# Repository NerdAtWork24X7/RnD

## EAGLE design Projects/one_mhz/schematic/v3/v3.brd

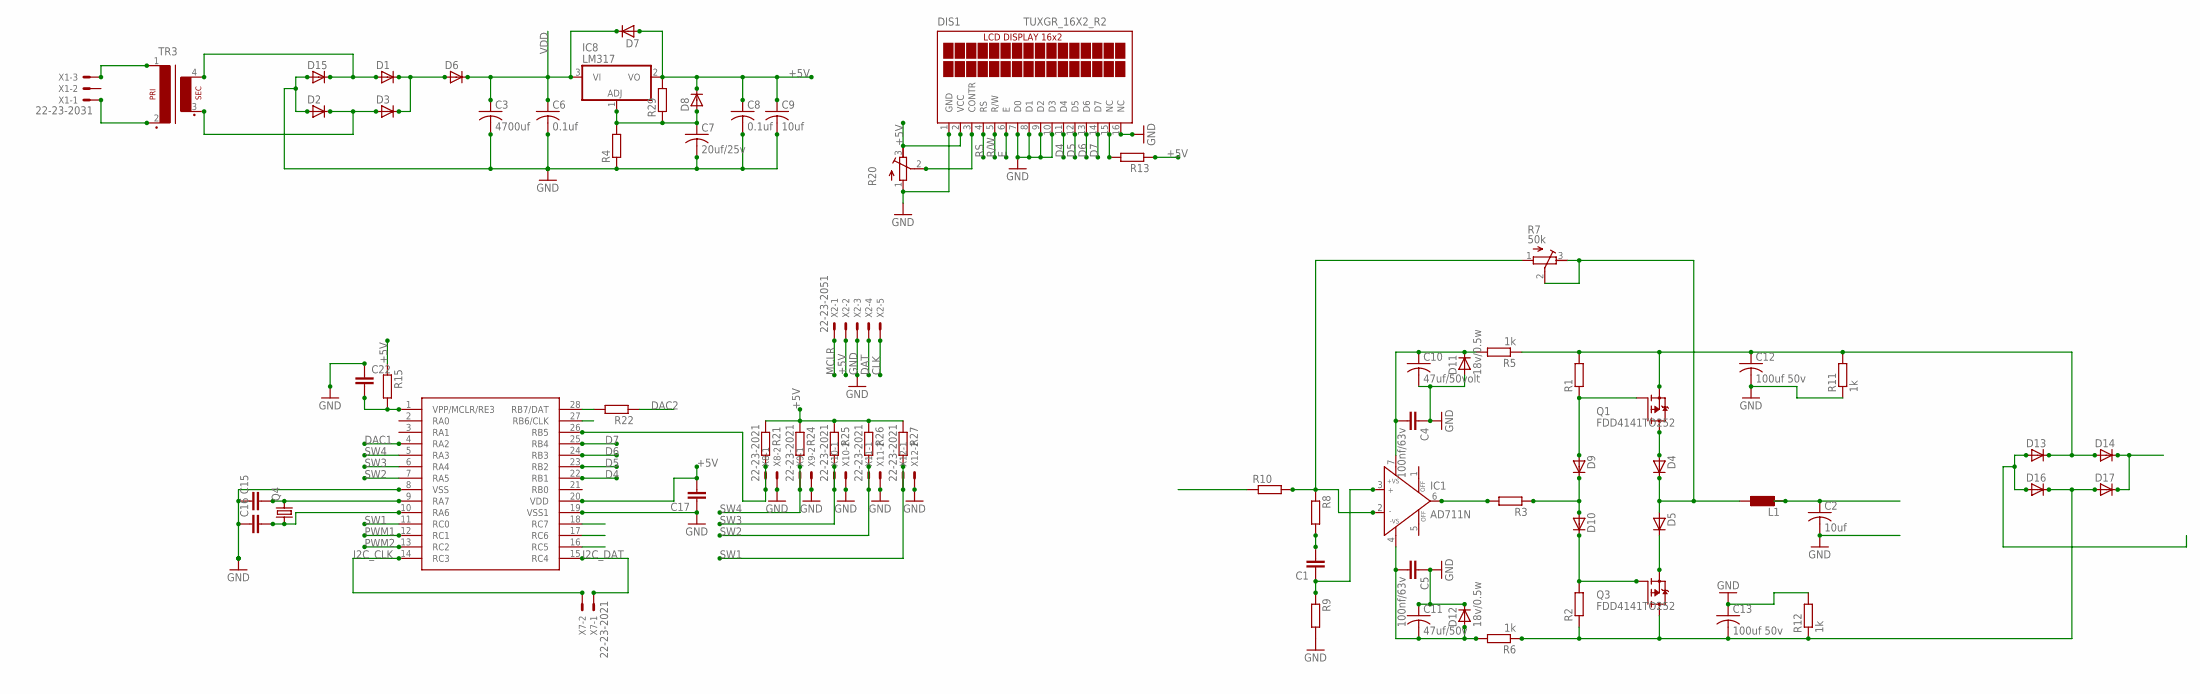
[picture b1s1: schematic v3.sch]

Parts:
C1, C15, C16, C17, C22: CC0603; C0603
C2, C9: 10uf; C025-025X050
C3: 4700uf; C025-025X050
C4, C5: 100nf/63v; C0603
C6, C8: 0.1uf; C025-025X050
C7: 20uf/25v; C025-025X050
C10: 47uf/50volt; C025-025X050
C11: 47uf/50v; C025-025X050
C12, C13: 100uf 50v; C025-025X050
D1, D2, D3, D4, D5, D6, D7, D8, D9, D10, D13, D14, D15, D16, D17: D-SOD-87; SOD87
D11, D12: 18v/0.5w; SOD87
DIS1: TUXGR_16X2_R2
IC1: AD711N; DIL08
IC8: LM317; TO92
L1: L0204/7; 0204/7
Q1, Q3: FDD4141TO252; TO252
Q4: CRYSTALHC49U-V; HC49U-V
R1, R2, R3, R4, R8, R9, R10, R13, R15, R21, R22, R24, R25, R26, R27, R29: R-EU_R0603; R0603
R5, R6, R11, R12: 1k; R0603
R7: 50k; RTRIM64X
R20: R-TRIMM64X; RTRIM64X
TR3: VR13-1
U$1: PIC16F15345; SO28W
X1: 22-23-2031
X2: 22-23-2051
X7, X8, X9, X10, X11, X12: 22-23-2021

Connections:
+5V: C8.1, C9.1, C17.2, D7.2 (A), D8.1 (C), DIS1.2 (VCC), IC8.2 (VO), R13.1, R15.1, R20.3 (E), R21.1, R24.1, R25.1, R26.1, R27.1, R29.2, U$1.20 (VDD), X2.2
CLK: U$1.27 (RB6/CLK), X2.5
D4: DIS1.11 (D4), U$1.22 (RB1)
D5: DIS1.12 (D5), U$1.23 (RB2)
D6: DIS1.13 (D6), U$1.24 (RB3)
D7: DIS1.14 (D7), U$1.25 (RB4)
DAC1: U$1.4 (RA2)
DAC2: R22.1
DAT: R22.2, U$1.28 (RB7/DAT), X2.4
E: DIS1.6 (E), U$1.18 (RC7)
GND: C2.2, C3.2, C4.1, C5.1, C6.2, C7.2, C8.2, C9.2, C10.2, C11.1, C12.2, C13.1, C15.1, C16.1, C17.1, C22.1, D2.2 (A), D11.2 (A), D12.1 (C), D15.2 (A), DIS1.1 (GND), DIS1.7 (D0), DIS1.8 (D1), DIS1.9 (D2), DIS1.10 (D3), DIS1.16 (NC), R4.1, R9.2, R11.1, R12.2, R20.1 (A), U$1.8 (VSS), U$1.19 (VSS1), X2.3, X8.2, X9.2, X10.2, X11.2, X12.2
GND1: D13.2 (A), D16.2 (A)
I2C_CLK: U$1.14 (RC3), X7.2
I2C_DAT: U$1.15 (RC4), X7.1
MCLR: C22.2, R15.2, U$1.1 (VPP/MCLR/RE3), X2.1
unnamed: D4.1 (C), D5.2 (A), L1.1, R7.2 (S), R7.3 (E)
unnamed: D4.2 (A), Q1.3 (D)
unnamed: D1.1 (C), D3.1 (C), D6.2 (A)
unnamed: D1.2 (A), D15.1 (C), TR3.4 (S4)
unnamed: D2.1 (C), D3.2 (A), TR3.3 (S3)
unnamed: D5.1 (C), Q3.2 (S)
unnamed: D9.1 (C), D10.2 (A), R3.1
unnamed: DIS1.15 (NC), R13.2
unnamed: D10.1 (C), Q3.1 (G), R2.2
unnamed: C7.1, D8.2 (A), IC8.1 (ADJ), R4.2, R29.1
unnamed: R21.2, U$1.26 (RB5), X8.1
unnamed: D9.2 (A), Q1.1 (G), R1.1
unnamed: IC1.6 (OUT), R3.2
unnamed: C5.2, C11.2, D12.2 (A), IC1.4 (-VS), R6.2
unnamed: C4.2, C10.1, D11.1 (C), IC1.7 (+VS), R5.2
unnamed: DIS1.3 (CONTR), R20.2 (S)
unnamed: C1.2, R8.2
unnamed: IC1.2 (IN-), R7.1 (A), R8.1, R10.2
unnamed: C1.1, IC1.3 (IN+), R9.1
unnamed: C2.1, L1.2
unnamed: D14.1 (C), D17.1 (C)
unnamed: C12.1, D13.1 (C), D14.2 (A), Q1.2 (S), R1.2, R5.1, R11.2
unnamed: TR3.1, X1.3
unnamed: TR3.2, X1.1
unnamed: C16.2, Q4.1, U$1.10 (RA6)
unnamed: C15.2, Q4.2, U$1.9 (RA7)
unnamed: C13.2, D16.1 (C), D17.2 (A), Q3.3 (D), R2.1, R6.1, R12.1
PWM1: U$1.12 (RC1)
PWM2: U$1.13 (RC2)
R/W: DIS1.5 (R/W), U$1.17 (RC6)
RS: DIS1.4 (RS), U$1.16 (RC5)
SW1: R27.2, U$1.11 (RC0), X12.1
SW2: R26.2, U$1.7 (RA5), X11.1
SW3: R25.2, U$1.6 (RA4), X10.1
SW4: R24.2, U$1.5 (RA3), X9.1
VDD: C3.1, C6.1, D6.1 (C), D7.1 (C), IC8.3 (VI)

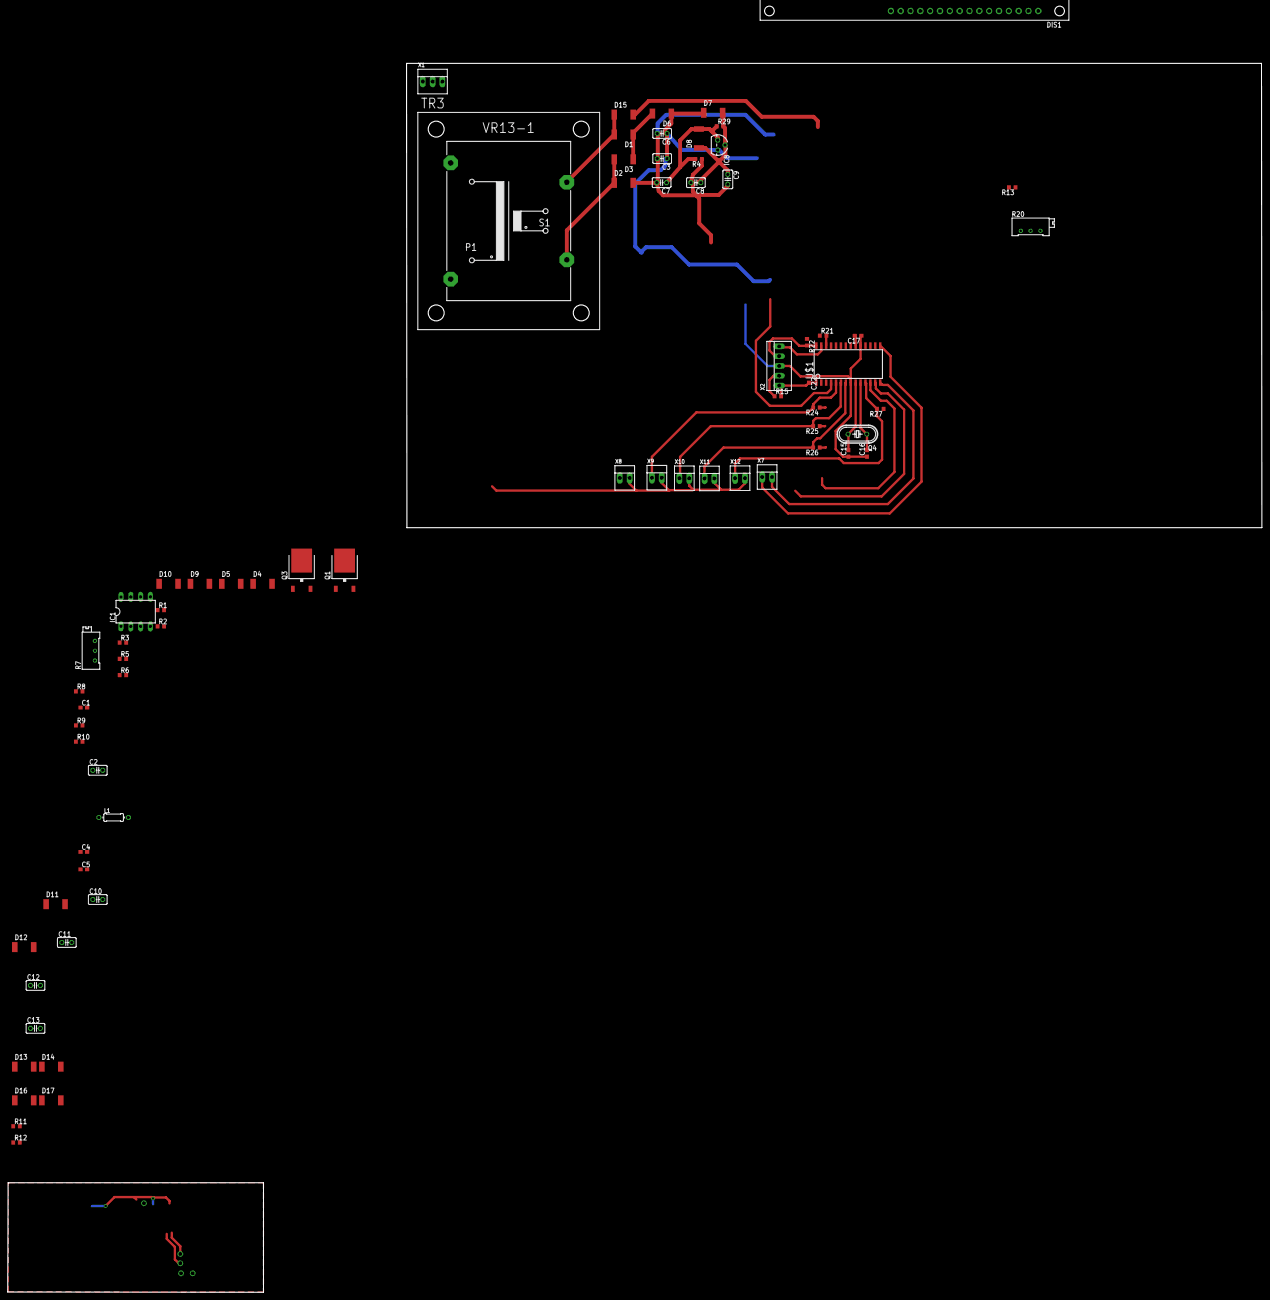
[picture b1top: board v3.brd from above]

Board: 2 copper layers, 324.1 x 317.6 mm, 73 parts (0 on the bottom side), 47 nets.

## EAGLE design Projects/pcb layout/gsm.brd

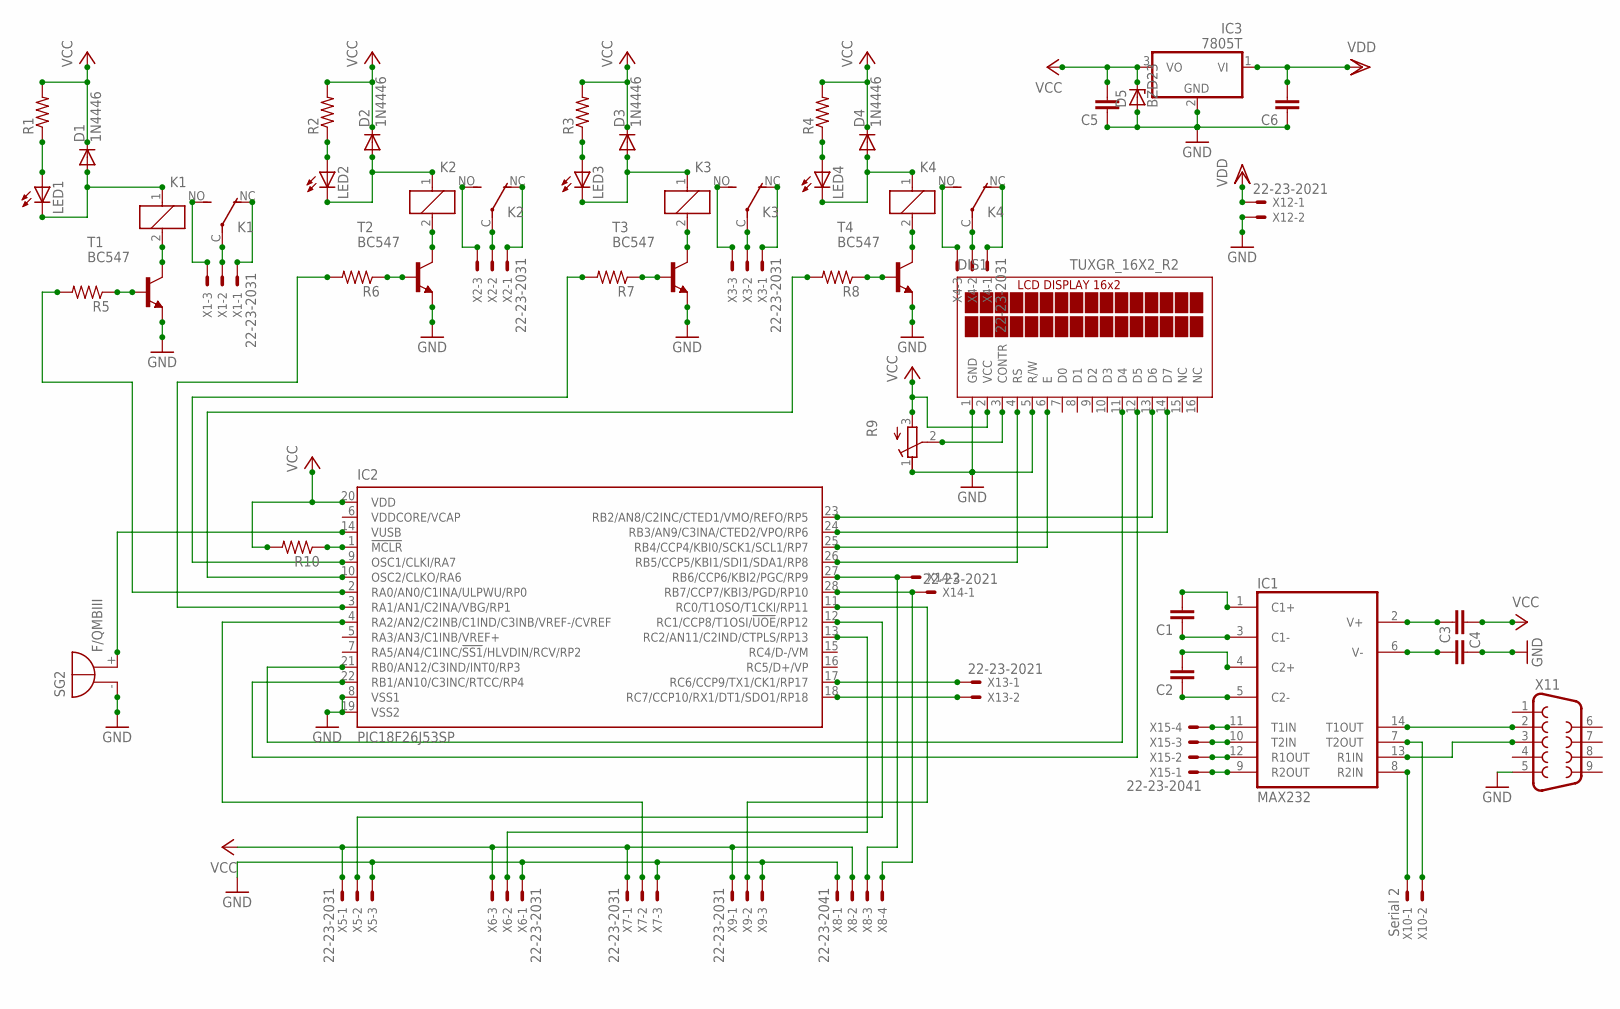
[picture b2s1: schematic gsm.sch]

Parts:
C1, C2, C3, C4, C5, C6: C2.5/2; C2.5-2
D1, D2, D3, D4: 1N4446; DO35-10
D5: BZD23; SOD81
DIS1: TUXGR_16X2_R2
IC1: MAX232; DIL16
IC2: PIC18F26J53SP; DIL28-3
IC3: 7805T; TO220H
K1, K2, K3, K4: JJM1-12V; JJM1C
LED1, LED2, LED3, LED4: LED3MM
R1, R2, R3, R4, R5, R6, R7, R8, R10: R-US_0207/10; 0207/10
R9: R-TRIMMT93YA; RTRIMT93YA
SG2: F/QMBIII
T1, T2, T3, T4: BC547; TO92
X1, X2, X3, X4, X5, X6, X7, X9: 22-23-2031
X8, X15: 22-23-2041
X10: Serial 2; 22-23-2021
X11: F09H
X12, X13, X14: 22-23-2021

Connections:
FIRERELAY: IC2.2 (RA0/AN0/C1INA/ULPWU/RP0), R5.2
GND: C3.2, C5.1, C6.1, D5.A, DIS1.1 (GND), DIS1.5 (R/W), IC1.15 (GND), IC2.8 (VSS1), IC2.19 (VSS2), IC3.2 (GND), R9.1 (E), SG2.- (+), T1.1 (E), T2.1 (E), T3.1 (E), T4.1 (E), X5.3, X6.1, X7.3, X8.1, X9.3, X11.5, X12.2
unnamed: K4.NC (O), X4.1
unnamed: LED1.A, R1.1
unnamed: D1.A, K1.1, LED1.K (C)
unnamed: K4.C, X4.2
unnamed: LED2.A, R2.1
unnamed: D2.A, K2.1, LED2.K (C)
unnamed: K4.NO (S), X4.3
unnamed: LED3.A, R3.1
unnamed: D3.A, K3.1, LED3.K (C)
unnamed: K3.NC (O), X3.1
unnamed: LED4.A, R4.1
unnamed: D4.A, K4.1, LED4.K (C)
unnamed: K1.2, T1.3 (C)
unnamed: K2.2, T2.3 (C)
unnamed: K3.2, T3.3 (C)
unnamed: K4.2, T4.3 (C)
unnamed: R5.1, T1.2 (B)
unnamed: R6.1, T2.2 (B)
unnamed: R7.1, T3.2 (B)
unnamed: R8.1, T4.2 (B)
unnamed: IC2.3 (RA1/AN1/C2INA/VBG/RP1), R6.2
unnamed: IC2.9 (OSC1/CLKI/RA7), R7.2
unnamed: IC2.10 (OSC2/CLKO/RA6), R8.2
unnamed: DIS1.14 (D7), IC2.24 (RB3/AN9/C3INA/CTED2/VPO/RP6)
unnamed: DIS1.13 (D6), IC2.23 (RB2/AN8/C2INC/CTED1/VMO/REFO/RP5)
unnamed: DIS1.12 (D5), IC2.22 (RB1/AN10/C3INC/RTCC/RP4)
unnamed: DIS1.11 (D4), IC2.21 (RB0/AN12/C3IND/INT0/RP3)
unnamed: DIS1.6 (E), IC2.25 (RB4/CCP4/KBI0/SCK1/SCL1/RP7)
unnamed: DIS1.4 (RS), IC2.26 (RB5/CCP5/KBI1/SDI1/SDA1/RP8)
unnamed: DIS1.3 (CONTR), R9.2 (S)
unnamed: K3.C, X3.2
unnamed: K3.NO (S), X3.3
unnamed: K2.C, X2.2
unnamed: K2.NC (O), X2.1
unnamed: K2.NO (S), X2.3
unnamed: K1.C, X1.2
unnamed: K1.NC (O), X1.1
unnamed: K1.NO (S), X1.3
unnamed: C1.2, IC1.1 (C1+)
unnamed: C1.1, IC1.3 (C1-)
unnamed: C2.2, IC1.4 (C2+)
unnamed: C2.1, IC1.5 (C2-)
unnamed: C4.2, IC1.2 (V+)
unnamed: C3.1, IC1.6 (V-)
unnamed: IC2.17 (RC6/CCP9/TX1/CK1/RP17), X13.1
unnamed: IC1.10 (T2IN), X15.3
unnamed: IC2.12 (RC1/CCP8/T1OSI/!UOE!/RP12), X5.2
unnamed: IC2.13 (RC2/AN11/C2IND/CTPLS/RP13), X6.2
unnamed: IC2.4 (RA2/AN2/C2INB/C1IND/C3INB/VREF-/CVREF), X7.2
unnamed: IC1.11 (T1IN), X15.4
unnamed: IC1.12 (R1OUT), X15.2
unnamed: IC2.27 (RB6/CCP6/KBI2/PGC/RP9), X8.3, X14.2
unnamed: IC2.1 (!MCLR), R10.1
unnamed: IC2.11 (RC0/T1OSO/T1CKI/RP11), X9.2
unnamed: IC2.14 (VUSB), SG2.+ (-)
unnamed: IC2.28 (RB7/CCP7/KBI3/PGD/RP10), X8.4, X14.1
unnamed: IC1.13 (R1IN), X11.3
unnamed: IC1.14 (T1OUT), X11.2
unnamed: IC1.7 (T2OUT), X10.2
unnamed: IC1.8 (R2IN), X10.1
unnamed: IC2.18 (RC7/CCP10/RX1/DT1/SDO1/RP18), X13.2
unnamed: IC1.9 (R2OUT), X15.1
VCC: C4.1, C5.2, D1.C, D2.C, D3.C, D4.C, D5.C, DIS1.2 (VCC), IC1.16 (VCC), IC2.20 (VDD), IC3.3 (VO), R1.2, R2.2, R3.2, R4.2, R9.3 (A), R10.2, X5.1, X6.3, X7.1, X8.2, X9.1
VDD: C6.2, IC3.1 (VI), X12.1

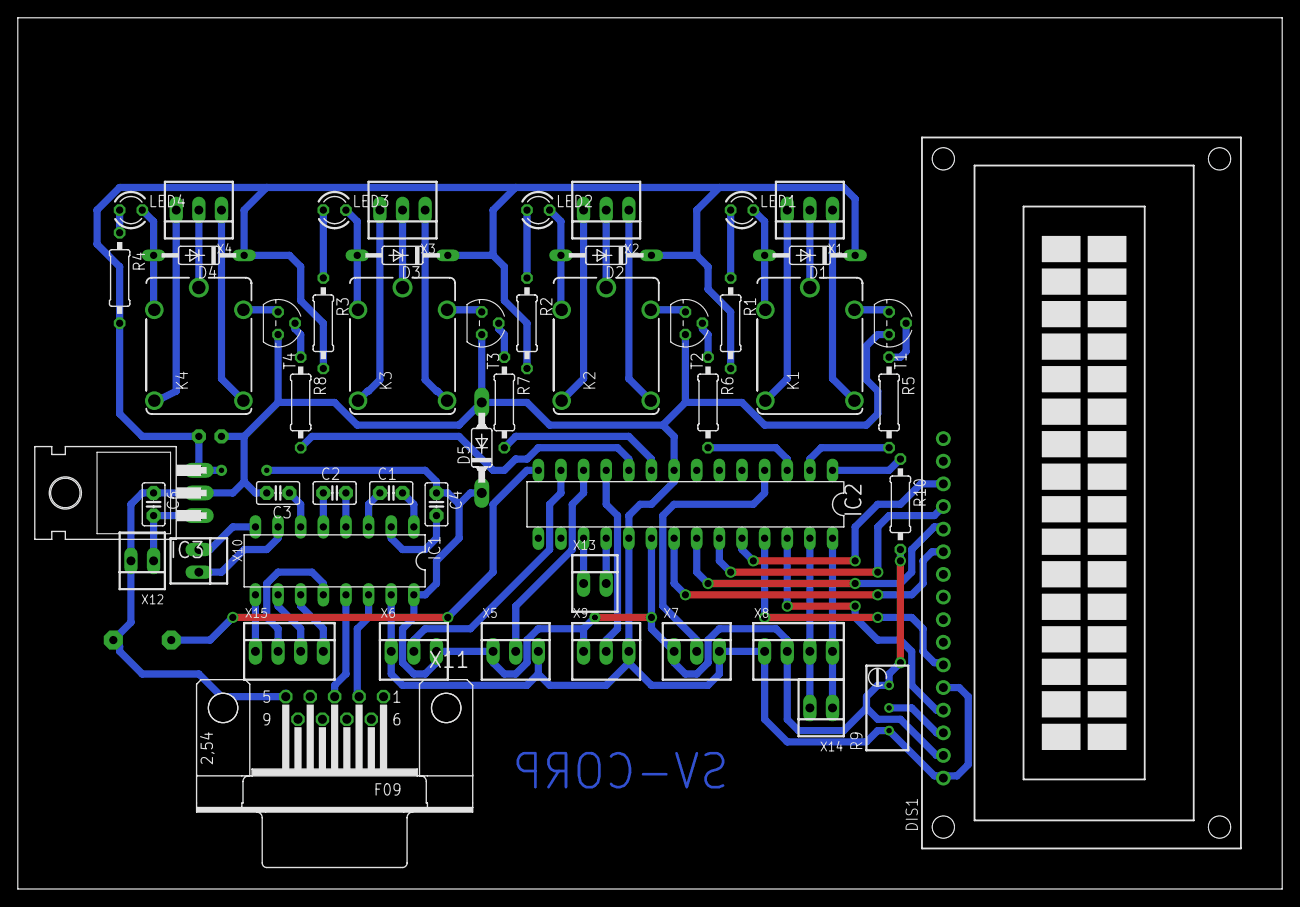
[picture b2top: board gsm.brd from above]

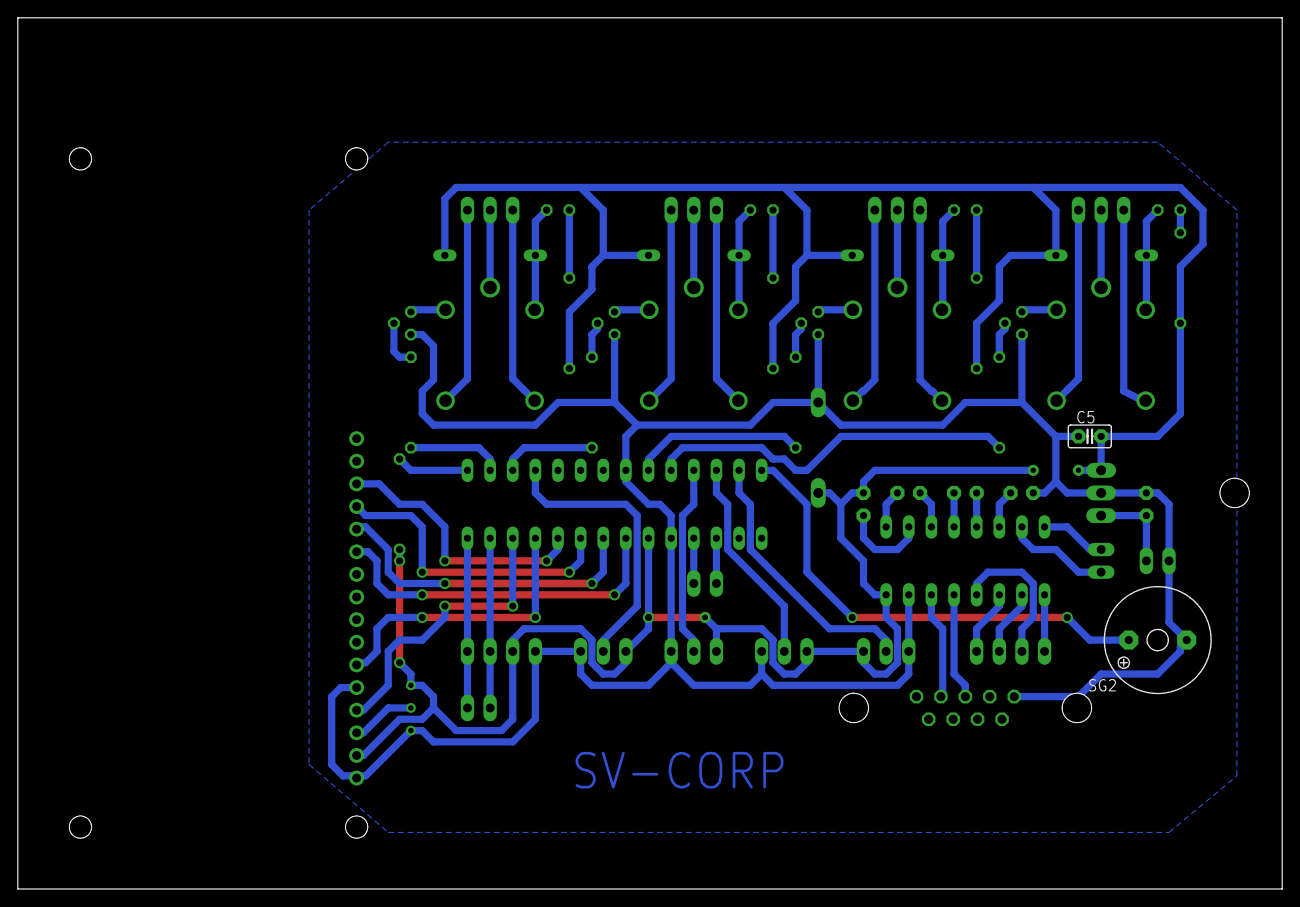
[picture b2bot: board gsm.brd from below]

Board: 2 copper layers, 141.9 x 97.8 mm, 53 parts (2 on the bottom side), 66 nets.

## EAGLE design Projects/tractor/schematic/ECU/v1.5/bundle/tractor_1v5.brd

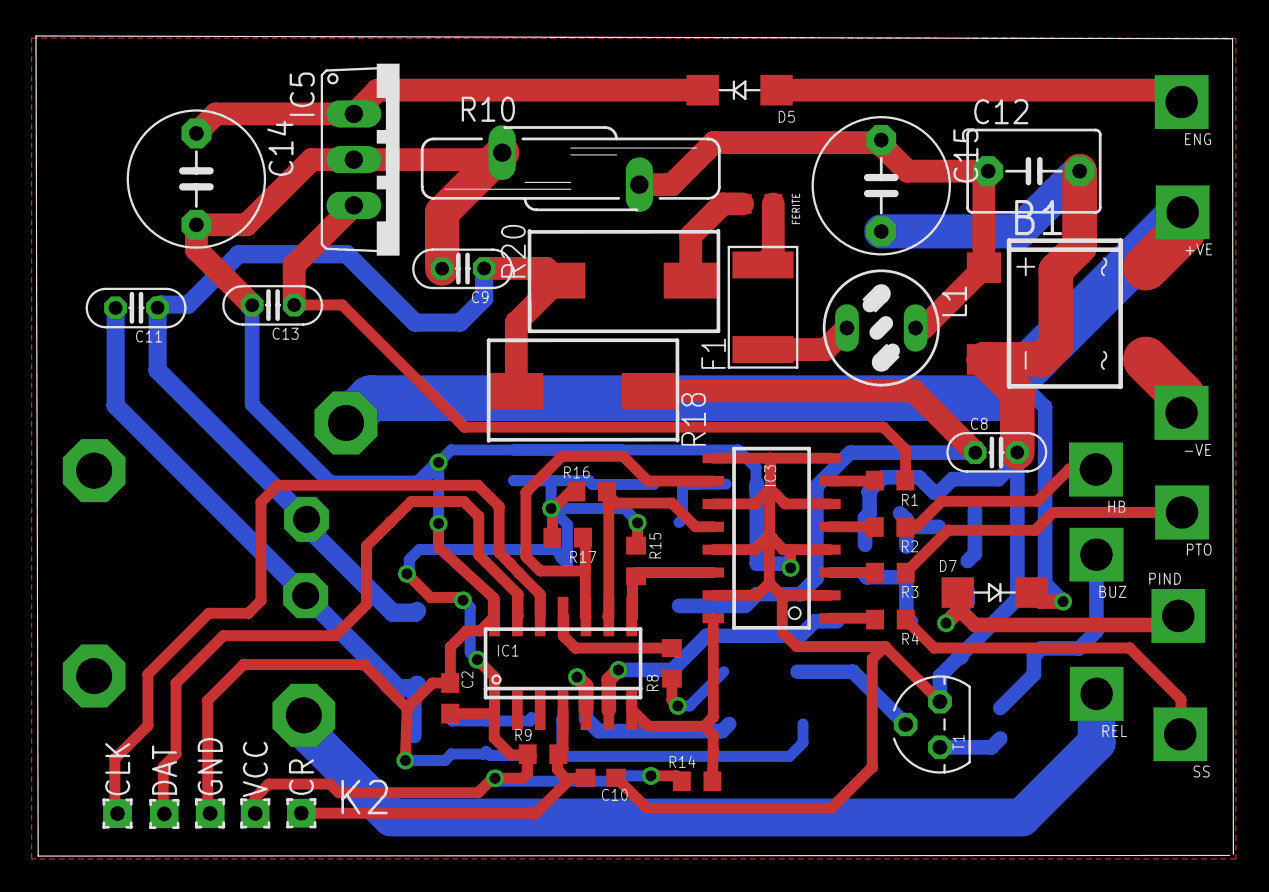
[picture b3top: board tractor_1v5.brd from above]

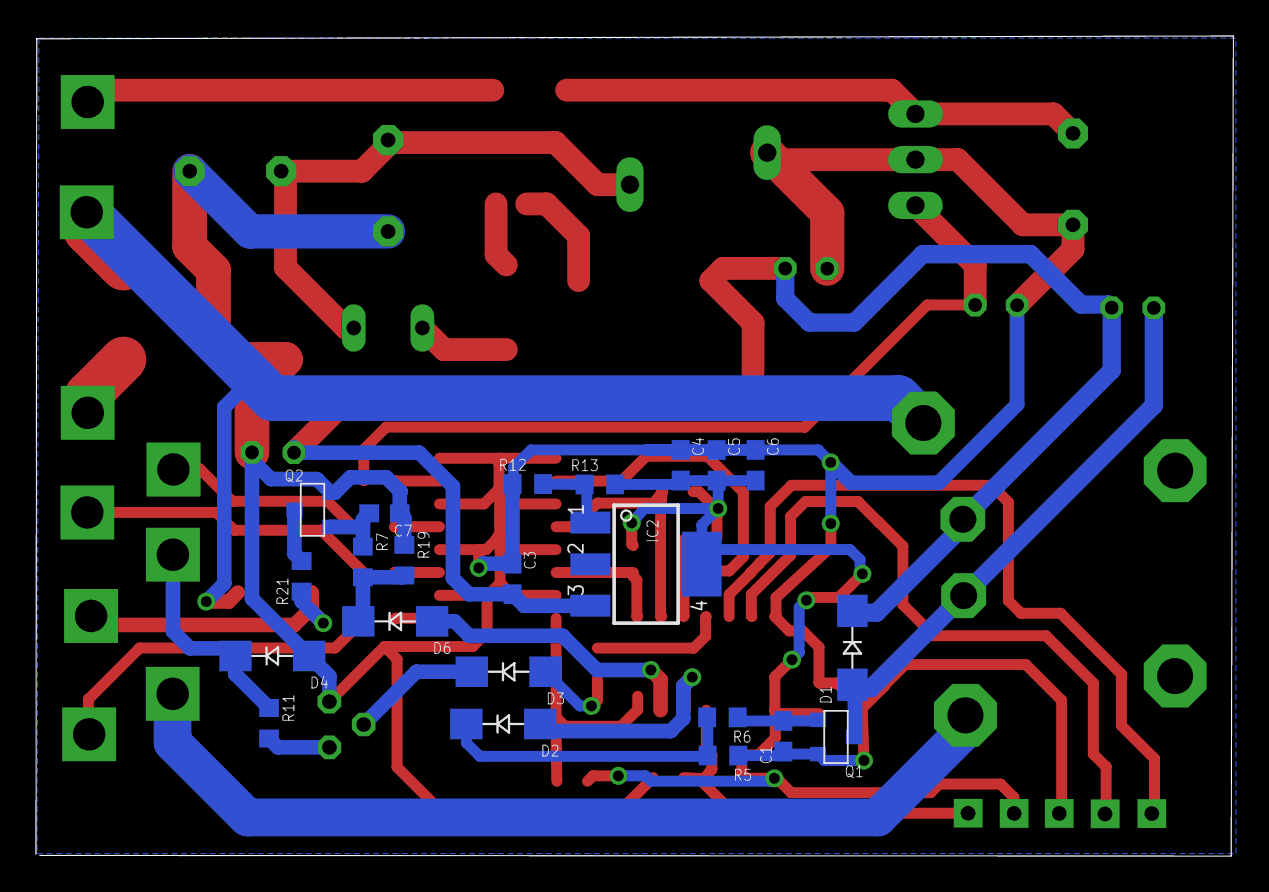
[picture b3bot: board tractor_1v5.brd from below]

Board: 2 copper layers, 66.5 x 45.6 mm, 69 parts (23 on the bottom side), 43 nets.

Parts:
+VE: 2,54/1,1
-VE: 2,54/1,1
B1: DBS106G; DBS
BUZ: 2,54/1,1
C1, C7: 1nf; C0603
C2, C3: 100nf; C0603
C4: 100nF; C0603
C5: 10nF; C0603
C6: 1uF; C0603
C8, C9, C11, C13: 220uf; C025-025X050
C10: 10uf; C0603
C12: 4nf; C050-045X075
C14, C15: 470uf; C050-075X075
CLK: 1,6/0,8
CR: 1,6/0,8
D1: LL4148; SMA-DO214AC
D2, D3, D4, D5, D6, D7: Fm4007; SMA-DO214AC
DAT: 1,6/0,8
ENG: 2,54/1,1
F1: RES_FUSE
FERITE: R0603
GND: 1,6/0,8
HB: 2,54/1,1
IC1: PIC16F1824; SO-14
IC2: 317EMP; SOT223
IC3: MINI-FLAT-16
IC5: 7812TV; TO220V
K2: RL703
L1: 3.3uH; 82114R
PIND: 2,54/1,1
PTO: 2,54/1,1
Q1, Q2: IRLML2402; MICRO3
R1, R2, R3, R4, R21: 1.5k; R0603
R5, R6, R7, R19: 10k; R0603
R8, R13: 470; R0603
R9: 10K; R0603
R10: S14K17
R11: 100; R0603
R12: 1k5; R0603
R14: 4.5K; R0603
R15, R16, R17: 4.5k; R0603
R18: 200; WSC2515
R20: 50; WSC2515
REL: 2,54/1,1
SS: 2,54/1,1
T1: BC547; TO92
VCC: 1,6/0,8

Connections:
12V_8: +VE.1, B1.AC1, D7.K, K2.NO
BUZZ_4: BUZ.1, D4.K, R11.1
ENG: D5.A, ENG.1
GND: B1.-, C1.1, C2.1, C3.1, C4.1, C5.1, C6.1, C7.1, C8.2, C9.2, C10.1, C12.2, C13.2, C14.2, C15.2, D4.A, GND.1, IC1.14, IC3.2, IC3.4, IC3.6, IC3.8, IC3.9, IC3.11, IC3.13, IC3.15, IC5.2, Q1.2, Q2.2, R5.1, R10.1, R12.1, R19.1, T1.1
HB_2: HB.1, R2.1
unnamed: -VE.1, B1.AC2
unnamed: IC1.10, IC3.10, R17.1
unnamed: C11.2, D1.A, K2.1, Q1.3
unnamed: C3.2, C8.1, IC2.3, R18.2
unnamed: DAT.1, IC1.13
unnamed: CLK.1, IC1.12
unnamed: C14.1, D5.K, IC5.1
unnamed: IC2.1, R12.2, R13.1
unnamed: FERITE.2, R20.1
unnamed: C13.1, IC5.3, R1.1
unnamed: F1.2, FERITE.1
unnamed: D2.K, R5.2, R6.2
unnamed: D3.A, R8.1
unnamed: F1.1, L1.2
unnamed: D2.A, IC1.5
unnamed: D6.A, IC1.6
unnamed: D6.K, R7.2, R19.2
unnamed: C7.2, Q2.1, R7.1
unnamed: D7.A, PIND.1, R21.1
unnamed: Q2.3, R21.2
unnamed: B1.+, C12.1, C15.1, L1.1, R10.2
unnamed: C1.2, Q1.1, R6.1
unnamed: IC3.1, R4.2
unnamed: IC3.3, R3.2
unnamed: IC3.5, R2.2
unnamed: IC3.7, R1.2
unnamed: IC1.9, IC3.12, R16.2
unnamed: IC1.8, IC3.14, R15.2
unnamed: IC1.7, IC3.16, R14.2
unnamed: C10.2, CR.1, IC1.4, R9.2
unnamed: IC1.11, R8.2
unnamed: D3.K, T1.2
unnamed: R11.2, T1.3
PTO_5: PTO.1, R3.1
R_3: K2.C1, REL.1
SS_6: R4.1, SS.1
VCC: C2.2, C4.2, C5.2, C6.2, IC1.1, IC2.4, R9.1, R13.2, R14.1, R15.1, R16.1, R17.2, VCC.1
VDD: C9.1, C11.1, D1.K, K2.2, R18.1, R20.2

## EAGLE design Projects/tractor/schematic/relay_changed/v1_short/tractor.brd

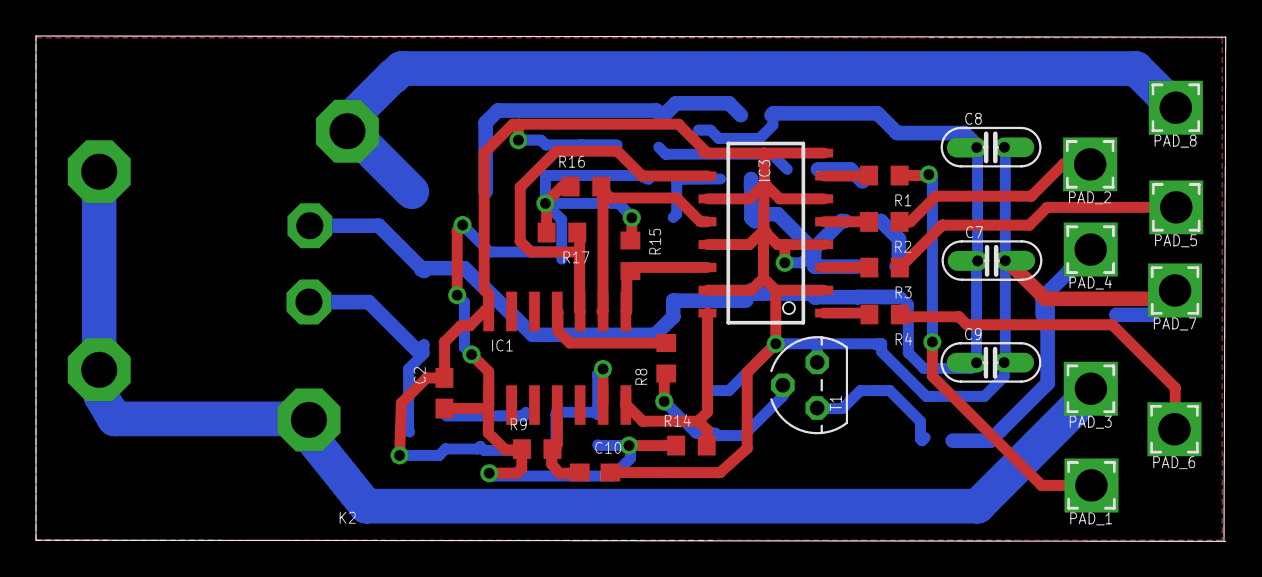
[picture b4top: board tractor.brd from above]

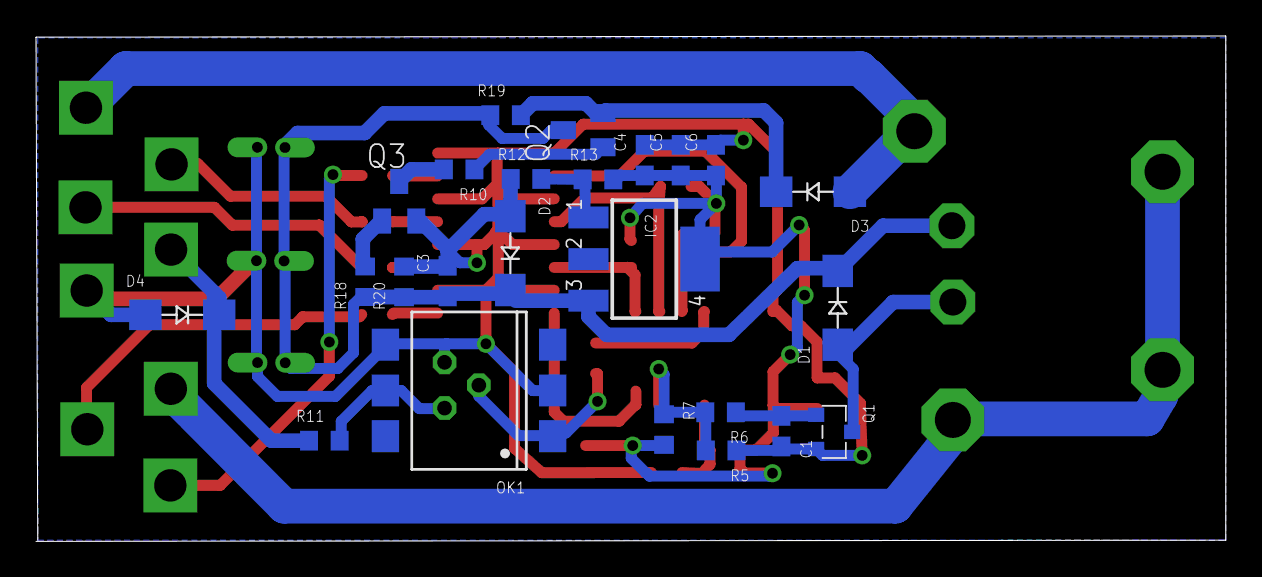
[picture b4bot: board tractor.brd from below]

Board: 2 copper layers, 66.1 x 28.1 mm, 51 parts (25 on the bottom side), 30 nets.

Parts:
C1: 1nf; C0603
C2, C3, C10: 100nf; C0603
C4: 100nF; C0603
C5: 10nF; C0603
C6: 1uF; C0603
C7, C8, C9: 220uf; C025-025X050
D1: LL4148; SMA-DO214AC
D2: 1N34; SMA-DO214AC
D3, D4: Fm4007; SMA-DO214AC
IC1: PIC16F1824; SO-14
IC2: 317EMP; SOT223
IC3: TLP283-4; MINI-FLAT-16
K2: RL703
OK1: H11L1MS; DIL6-SMD
PAD_1, PAD_2, PAD_3, PAD_4, PAD_5, PAD_6, PAD_7, PAD_8: 2,54/1,1
Q1: IRLML2402; MICRO3
Q2, Q3: SOT23
R1, R2, R3, R4, R10: 1k; R0603
R5, R6, R20: 10k; R0603
R7, R14, R15, R16, R17: 1K; R0603
R8, R11, R13: 470; R0603
R9: 10K; R0603
R12: 1k5; R0603
R18: 270R; R0603
R19: 220; R0603
T1: BC547; TO92

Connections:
12V_8: D3.A, K2.NO, PAD_8.1
BUZZ_4: D4.K, PAD_4.1, R11.1
GND: C1.1, C2.1, C3.1, C4.1, C5.1, C6.1, C7.2, C8.2, C9.2, C10.1, D2.A, D4.A, IC1.14, IC3.2, IC3.4, IC3.6, IC3.8, IC3.9, IC3.11, IC3.13, IC3.15, OK1.2, OK1.4, PAD_7.1, Q1.2, Q3.2, R5.1, R12.1, R20.2, T1.1
GR_1: PAD_1.1, R1.1
HB_2: PAD_2.1, R2.1
unnamed: IC1.10, IC3.10, R17.1
unnamed: D1.A, K2.1, Q1.3
unnamed: Q2.1, R10.1
unnamed: Q3.1, R18.2
unnamed: Q3.3, R10.2
unnamed: D3.K, Q2.2, R19.2
unnamed: IC2.1, R12.2, R13.1
unnamed: C1.2, Q1.1, R6.1
unnamed: IC1.6, R5.2, R6.2, R7.1
unnamed: IC3.1, R4.2
unnamed: IC3.3, R3.2
unnamed: IC3.5, R2.2
unnamed: IC3.7, R1.2
unnamed: IC1.9, IC3.12, R16.2
unnamed: IC1.8, IC3.14, R15.2
unnamed: IC1.7, IC3.16, R14.2
unnamed: C10.2, IC1.4, R9.2
unnamed: IC1.11, R8.2
unnamed: OK1.1, R8.1, T1.2
unnamed: OK1.5, R11.2, T1.3
PTO_5: PAD_5.1, R3.1
R_3: K2.C1, K2.C2, K2.C3, PAD_3.1
SS_6: PAD_6.1, R4.1
VCC: C2.2, C4.2, C5.2, C6.2, IC1.1, IC2.4, R7.2, R9.1, R13.2, R14.1, R15.1, R16.1, R17.2
VDD: C3.2, C7.1, C8.1, C9.1, D1.K, D2.K, IC2.3, K2.2, Q2.3, R18.1, R19.1, R20.1

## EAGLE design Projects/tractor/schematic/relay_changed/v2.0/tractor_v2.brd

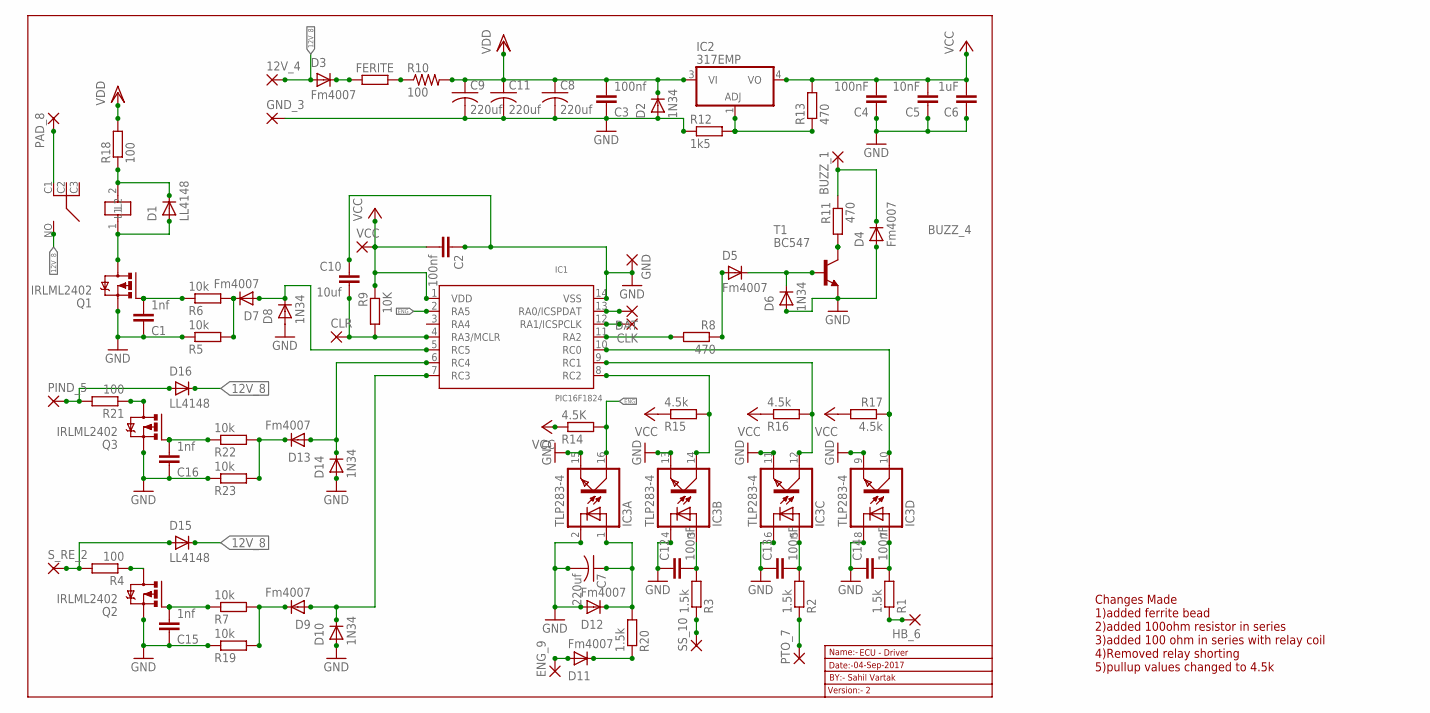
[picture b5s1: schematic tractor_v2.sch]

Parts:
12V_4: 2,54/1,1
BUZZ_1: 2,54/1,1
C1, C15, C16: 1nf; C0603
C2, C3: 100nf; C0603
C4, C12, C13, C14: 100nF; C0603
C5: 10nF; C0603
C6: 1uF; C0603
C7, C8, C9, C11: 220uf; C025-025X050
C10: 10uf; C0603
CLK: 1,6/0,8
CLR: 1,6/0,8
D1, D15, D16: LL4148; SMA-DO214AC
D2, D6, D8, D10, D14: 1N34; SMA-DO214AC
D3, D4, D5, D7, D9, D11, D12, D13: Fm4007; SMA-DO214AC
DAT: 1,6/0,8
ENG_9: 2,54/1,1
FERITE: R-EU_R0603; R0603
GND: 1,6/0,8
GND_3: 2,54/1,1
HB_6: 2,54/1,1
IC1: PIC16F1824; SO-14
IC2: 317EMP; SOT223
IC3: TLP283-4; MINI-FLAT-16
K2: RL703
PAD_8: 2,54/1,1
PIND_5: 2,54/1,1
PTO_7: 2,54/1,1
Q1, Q2, Q3: IRLML2402; MICRO3
R1, R2, R3, R20: 1.5k; R0603
R4, R18, R21: 100; R0603
R5, R6, R7, R19, R22, R23: 10k; R0603
R8, R11, R13: 470; R0603
R9: 10K; R0603
R10: 100; WSC2515
R12: 1k5; R0603
R14: 4.5K; R0603
R15, R16, R17: 4.5k; R0603
SS_10: 2,54/1,1
S_RE_2: 2,54/1,1
T1: BC547; TO92
VCC: 1,6/0,8

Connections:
12V_8: 12V_4.1, D3.A, D15.K (C), D16.K (C), K2.NO
BUZZ_4: BUZZ_1.1, D4.K (C), R11.1
ENG: IC1.2 (RA5), IC3.16 (COL), R14.2
GND: C1.1, C2.1, C3.1, C4.1, C5.1, C6.1, C7.2, C8.2, C9.2, C10.1, C11.2, C12.1, C13.1, C14.1, C15.1, C16.1, D2.A, D4.A, D6.A, D8.A, D10.A, D12.A, D14.A, GND.1, GND_3.1, IC1.14 (VSS), IC3.2 (C), IC3.4 (C), IC3.6 (C), IC3.8 (C), IC3.9 (EMIT), IC3.11 (EMIT), IC3.13 (EMIT), IC3.15 (EMIT), Q1.2 (S), Q2.2 (S), Q3.2 (S), R5.1, R12.1, R19.1, R23.1, T1.1 (E)
unnamed: D11.K (C), R20.1
unnamed: IC1.10 (RC0), IC3.10 (COL), R17.1
unnamed: D1.A, K2.1 (L2), Q1.3 (D)
unnamed: C16.2, Q3.1 (G), R22.1
unnamed: D3.K (C), FERITE.1
unnamed: DAT.1, IC1.13 (RA0/ICSPDAT)
unnamed: CLK.1, IC1.12 (RA1/ICSPCLK)
unnamed: D1.K (C), K2.2 (L1), R18.1
unnamed: IC2.1 (ADJ), R12.2, R13.1
unnamed: FERITE.2, R10.1
unnamed: D5.A, R8.1
unnamed: D7.A, D8.K (C), IC1.5 (RC5)
unnamed: C15.2, Q2.1 (G), R7.1
unnamed: D9.K (C), R7.2, R19.2
unnamed: Q2.3 (D), R4.1
unnamed: D11.A, ENG_9.1
unnamed: C7.1, D12.K (C), IC3.1 (A), R20.2
unnamed: D13.K (C), R22.2, R23.2
unnamed: D16.A, PIND_5.1, R21.2
unnamed: D13.A, D14.K (C), IC1.6 (RC4)
unnamed: D15.A, R4.2, S_RE_2.1
unnamed: Q3.3 (D), R21.1
unnamed: HB_6.1, R1.1
unnamed: R3.1, SS_10.1
unnamed: PTO_7.1, R2.1
unnamed: D9.A, D10.K (C), IC1.7 (RC3)
unnamed: C1.2, Q1.1 (G), R6.1
unnamed: D7.K (C), R5.2, R6.2
unnamed: C12.2, IC3.3 (A), R3.2
unnamed: C13.2, IC3.5 (A), R2.2
unnamed: C14.2, IC3.7 (A), R1.2
unnamed: IC1.9 (RC1), IC3.12 (COL), R16.2
unnamed: IC1.8 (RC2), IC3.14 (COL), R15.2
unnamed: C10.2, CLR.1, IC1.4 (RA3/MCLR), R9.2
unnamed: IC1.11 (RA2), R8.2
unnamed: D5.K (C), D6.K (C), T1.2 (B)
unnamed: R11.2, T1.3 (C)
R_3: K2.C1, PAD_8.1
VCC: C2.2, C4.2, C5.2, C6.2, IC1.1 (VDD), IC2.4 (VO), R9.1, R13.2, R14.1, R15.1, R16.1, R17.2, VCC.1
VDD: C3.2, C8.1, C9.1, C11.1, D2.K (C), IC2.3 (VI), R10.2, R18.2

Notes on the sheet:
Name:-
Version:- 2
Date:-
ECU - Driver
BY:- Sahil Vartak
04-Sep-2017
Changes Made 1)added ferrite bead 2)added 100ohm resistor in series 3)added 100 ohm in series with relay coil 4)Removed relay shorting 5)pullup values changed to 4.5k

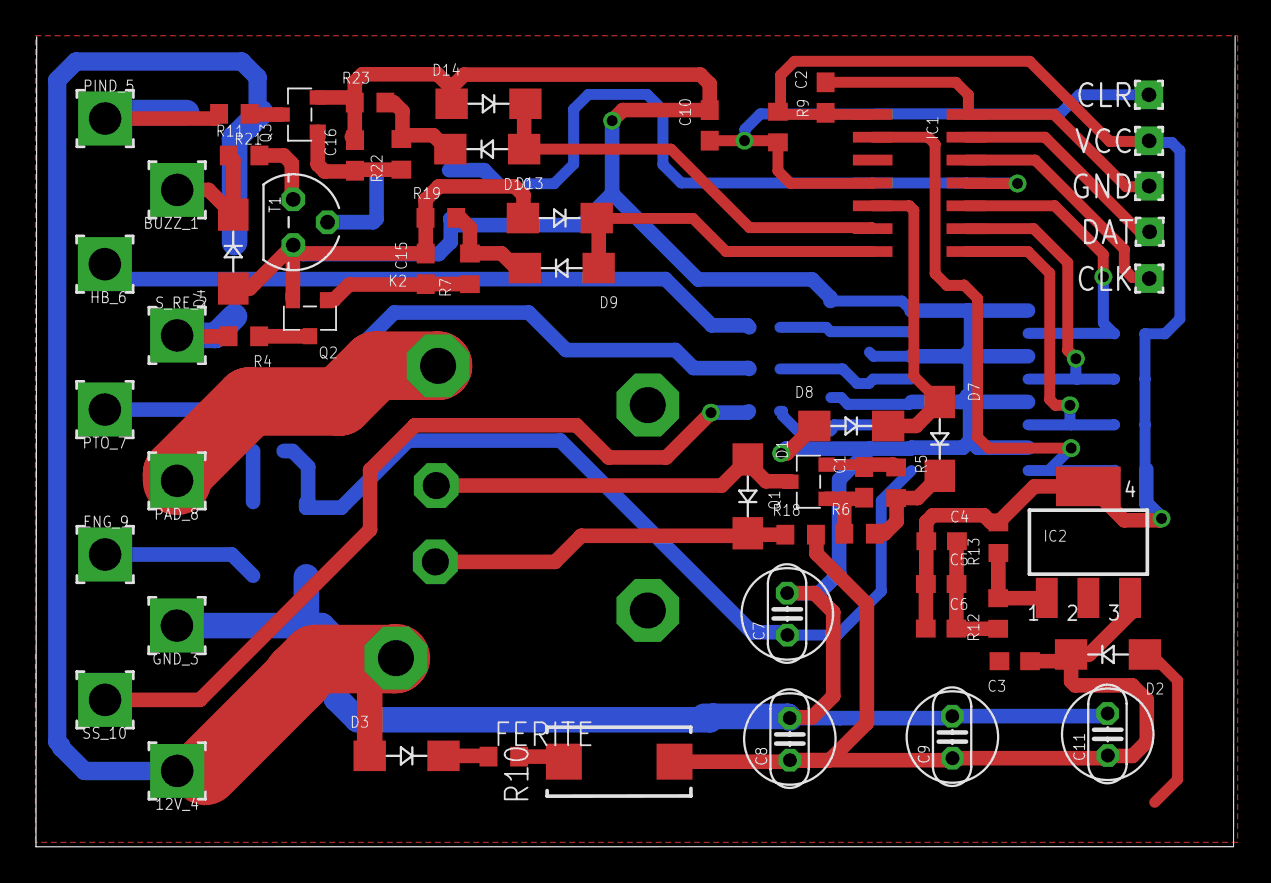
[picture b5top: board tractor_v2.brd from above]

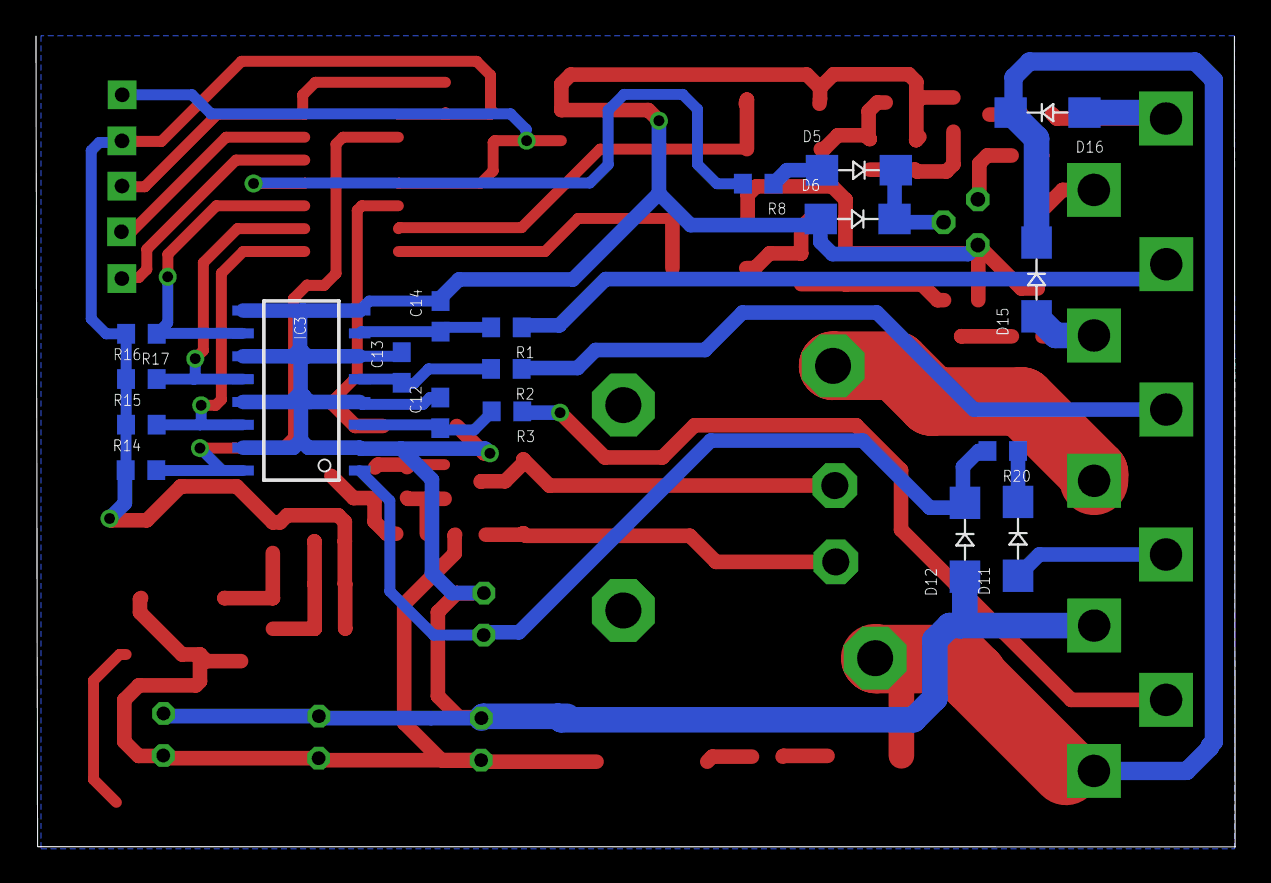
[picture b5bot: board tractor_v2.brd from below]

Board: 2 copper layers, 66.6 x 45.0 mm, 79 parts (20 on the bottom side), 44 nets.
